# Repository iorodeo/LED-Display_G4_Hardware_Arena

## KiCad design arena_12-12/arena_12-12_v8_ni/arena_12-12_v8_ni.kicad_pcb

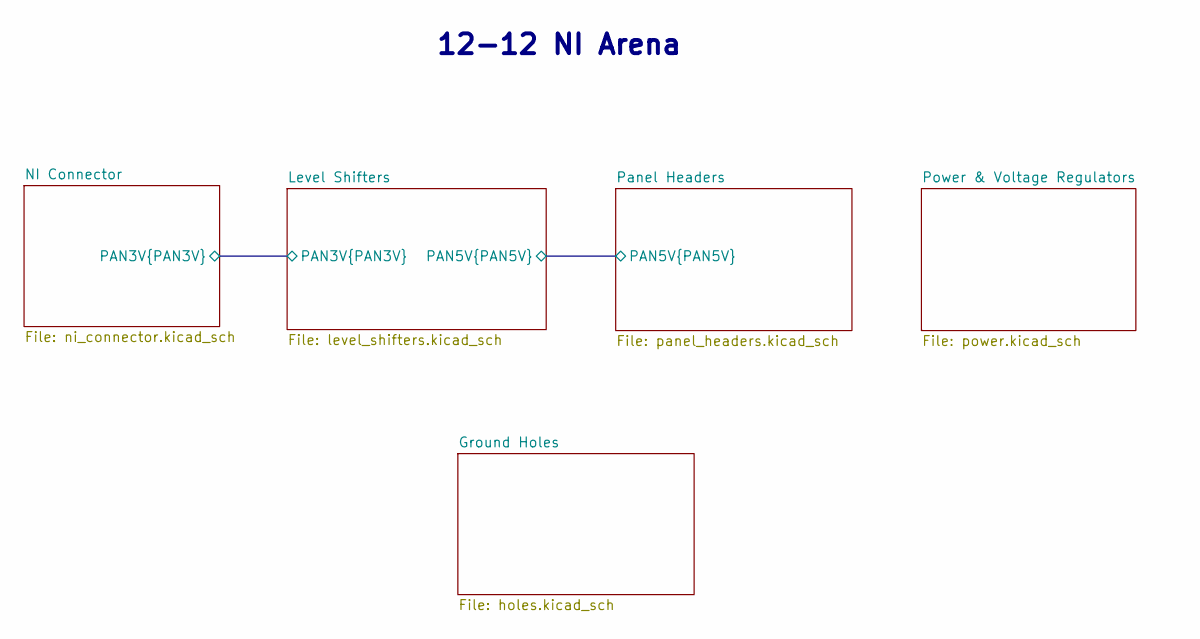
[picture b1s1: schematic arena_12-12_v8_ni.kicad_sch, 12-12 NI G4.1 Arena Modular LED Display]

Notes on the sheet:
12-12 NI Arena

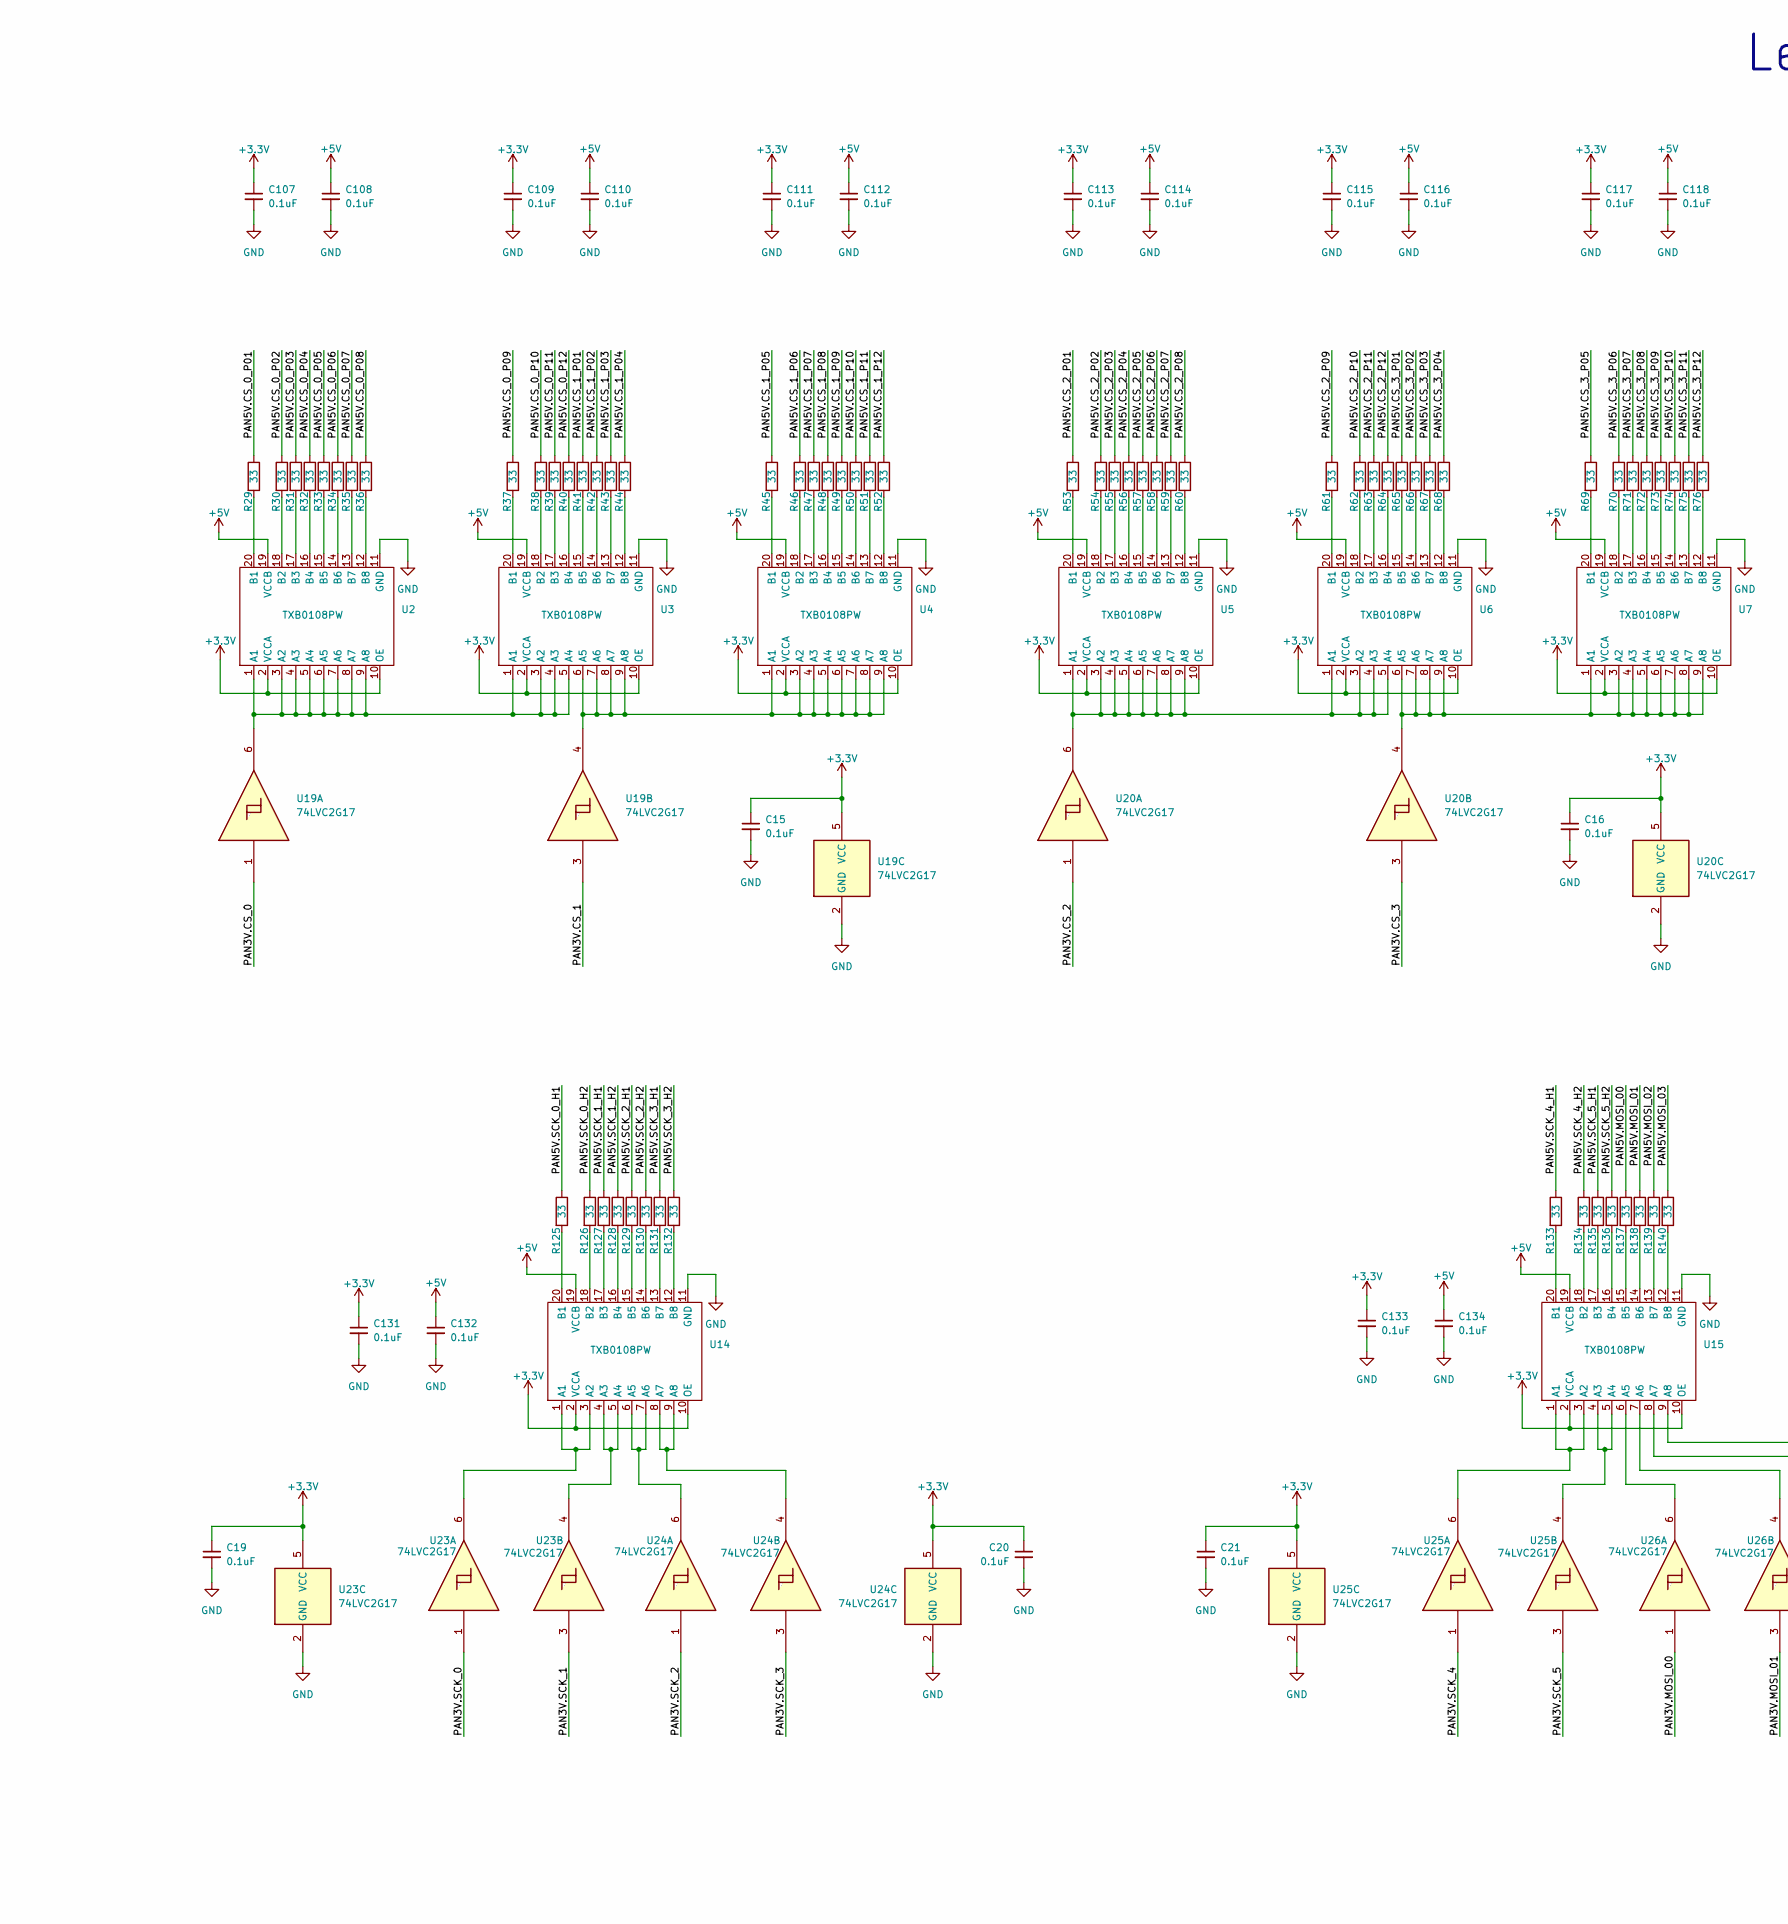
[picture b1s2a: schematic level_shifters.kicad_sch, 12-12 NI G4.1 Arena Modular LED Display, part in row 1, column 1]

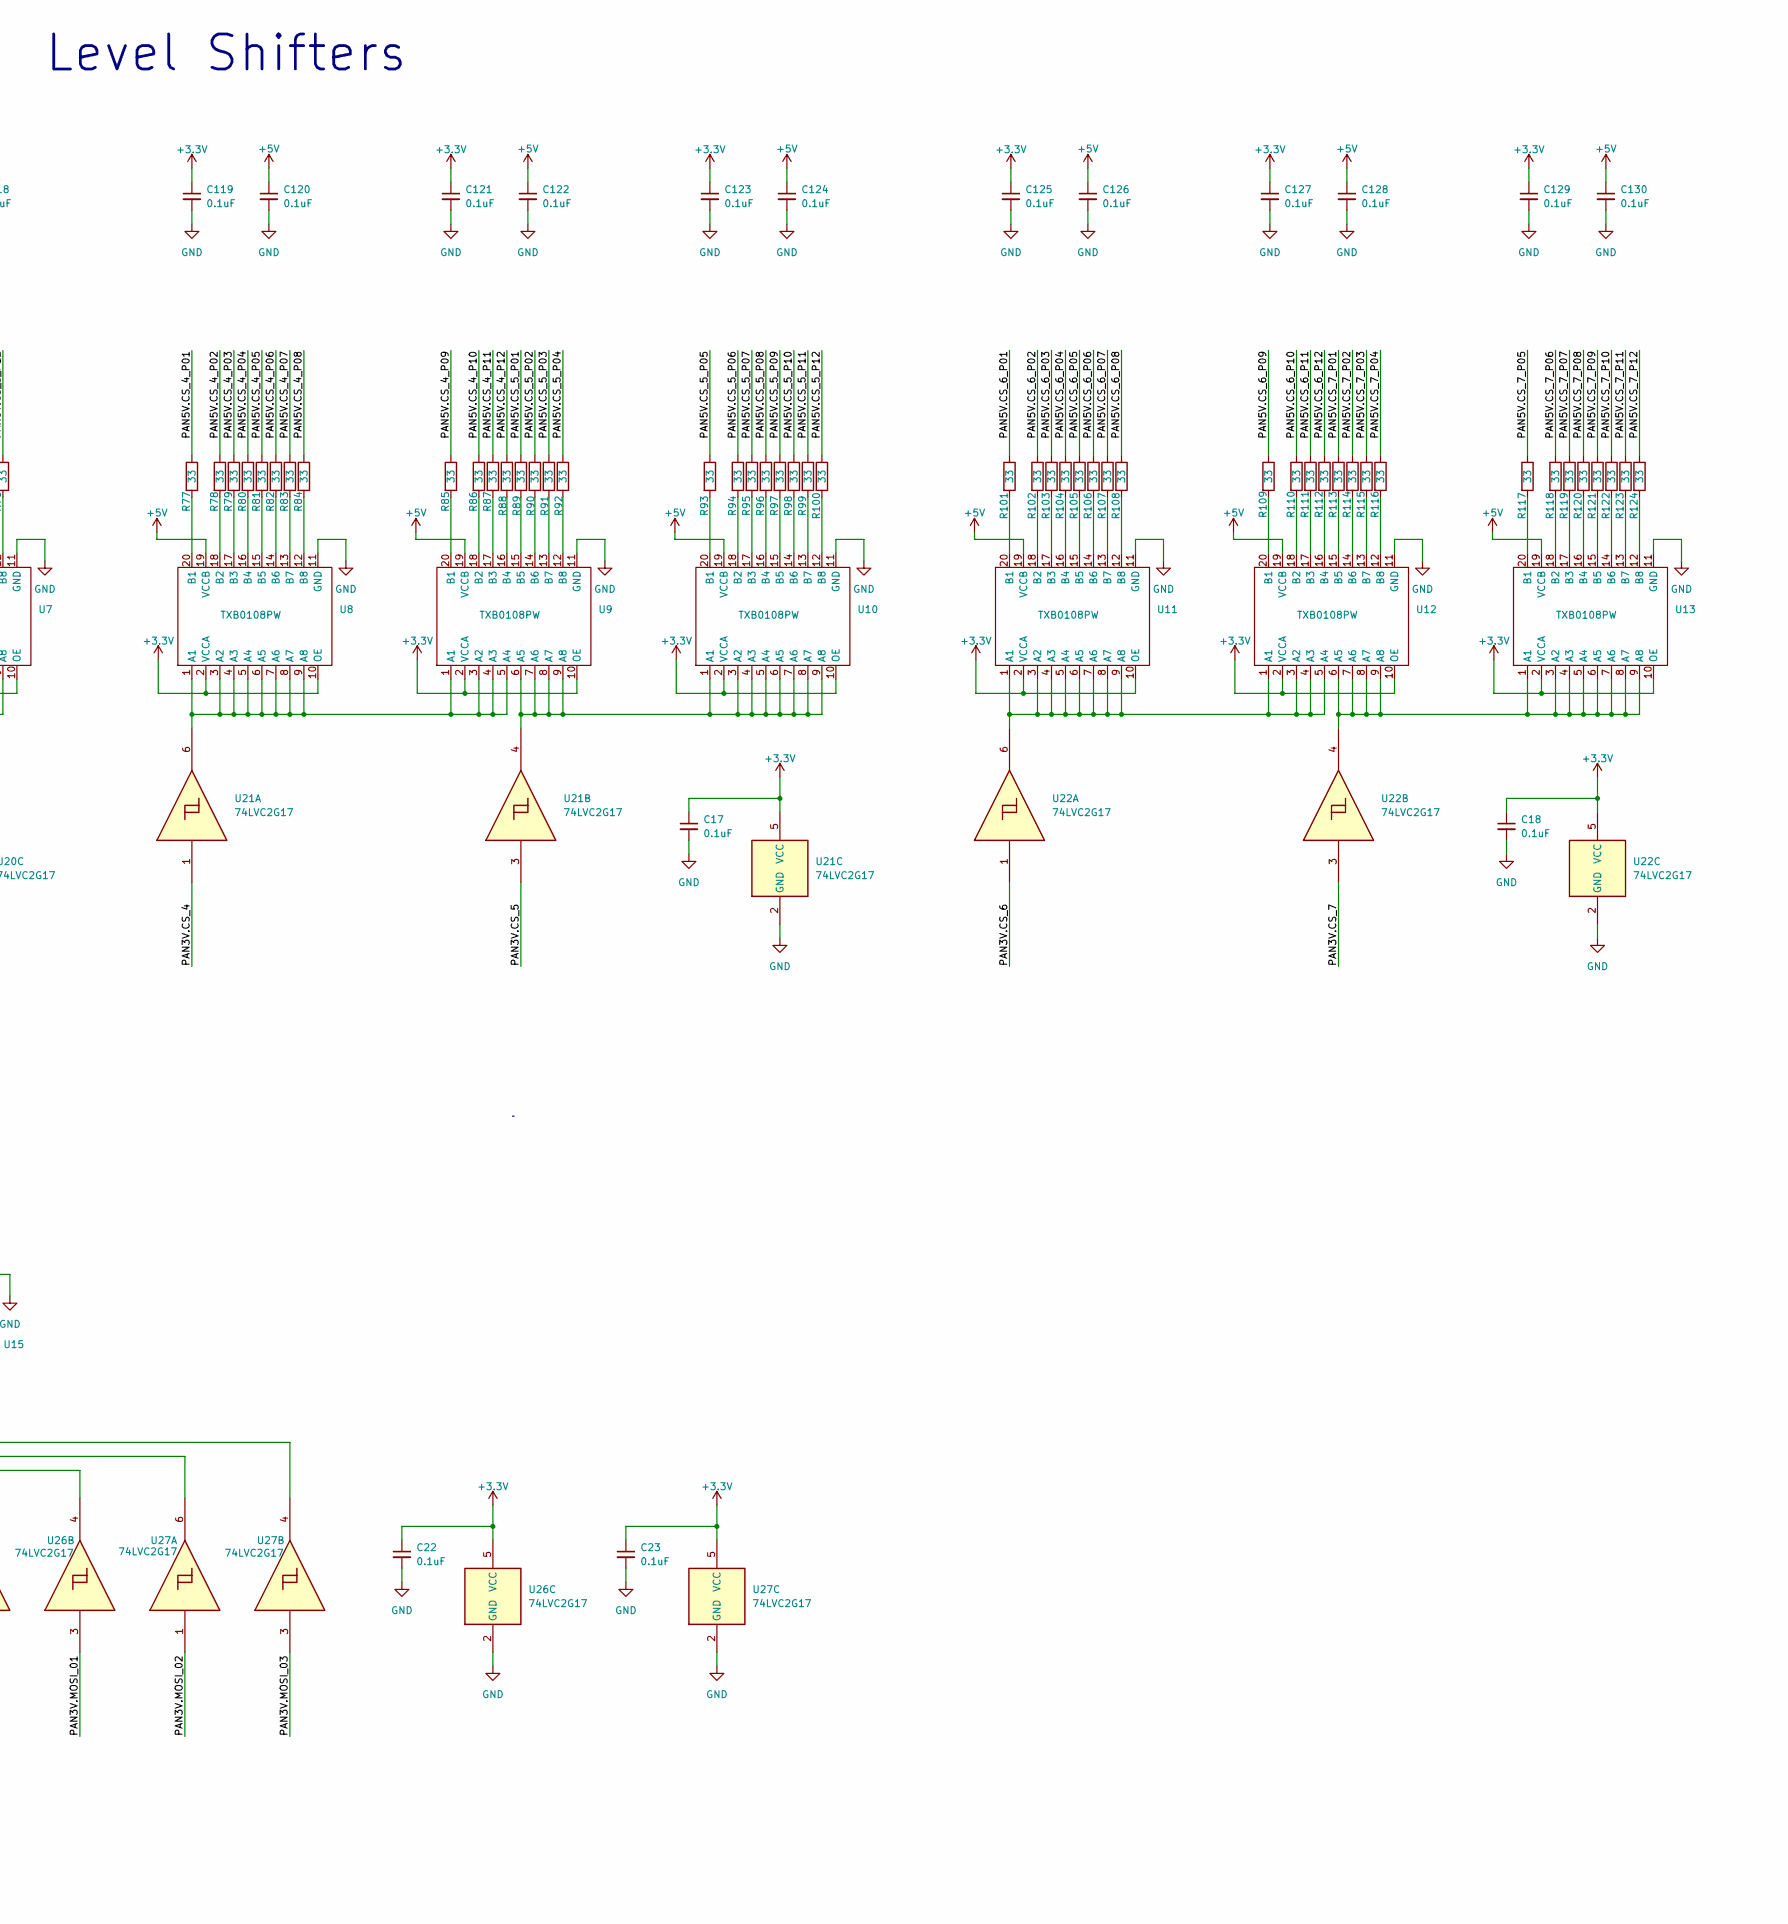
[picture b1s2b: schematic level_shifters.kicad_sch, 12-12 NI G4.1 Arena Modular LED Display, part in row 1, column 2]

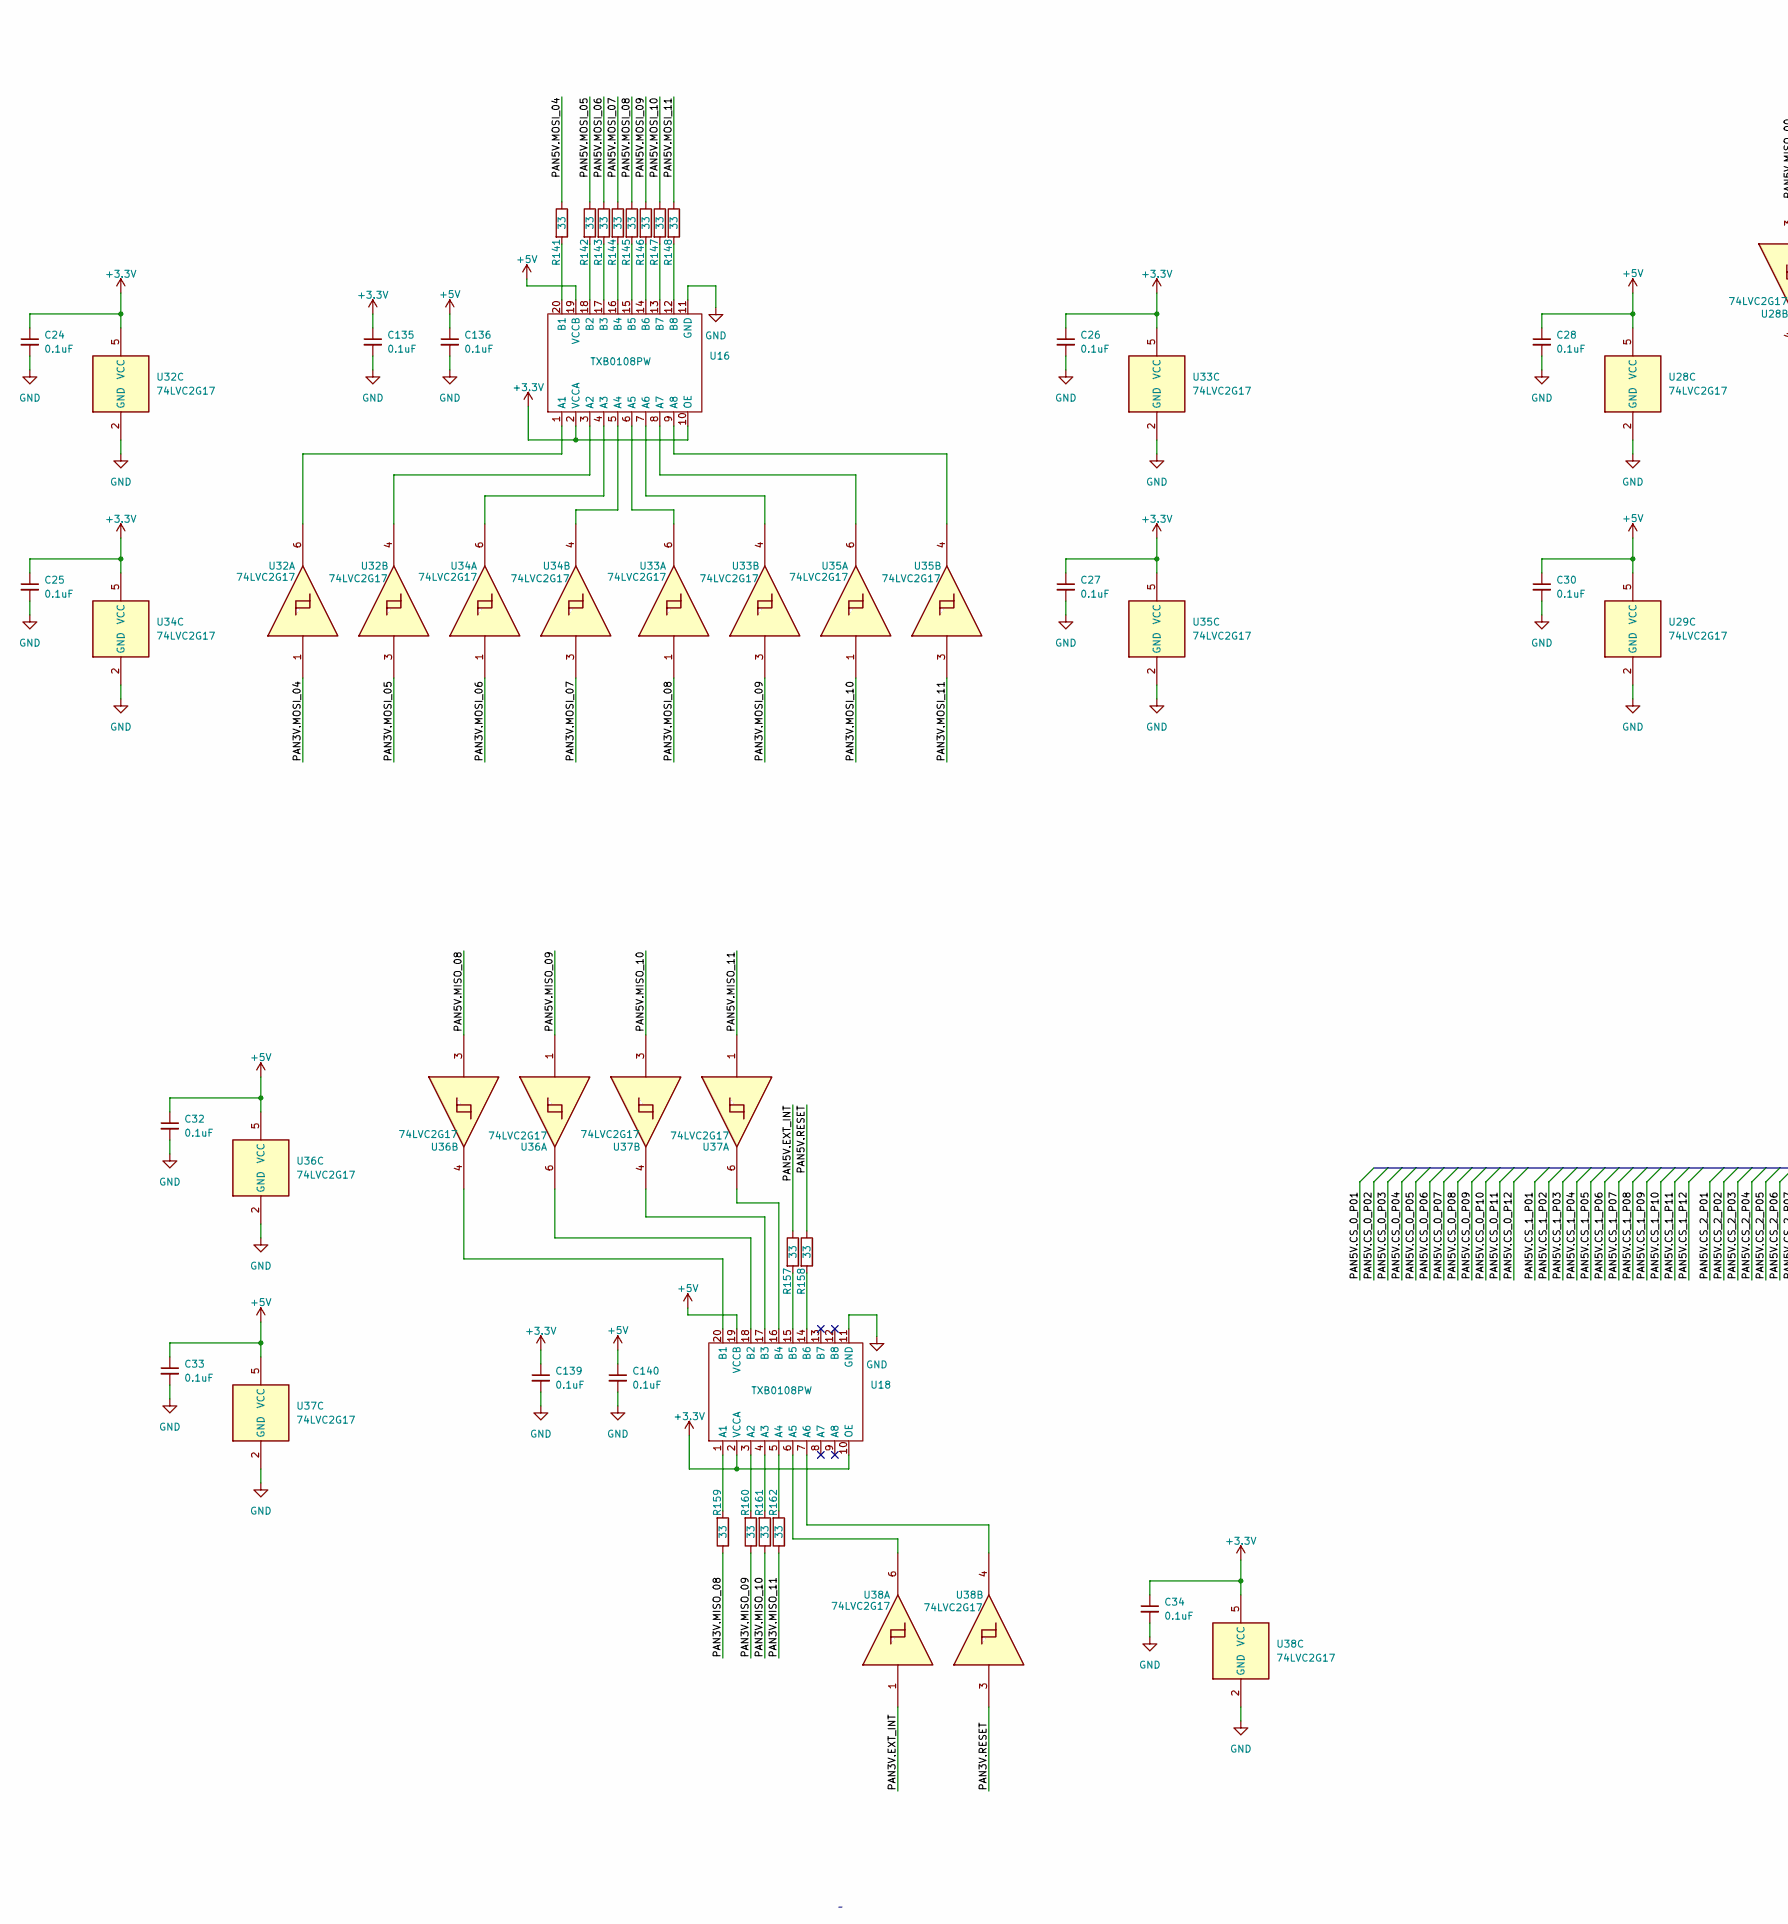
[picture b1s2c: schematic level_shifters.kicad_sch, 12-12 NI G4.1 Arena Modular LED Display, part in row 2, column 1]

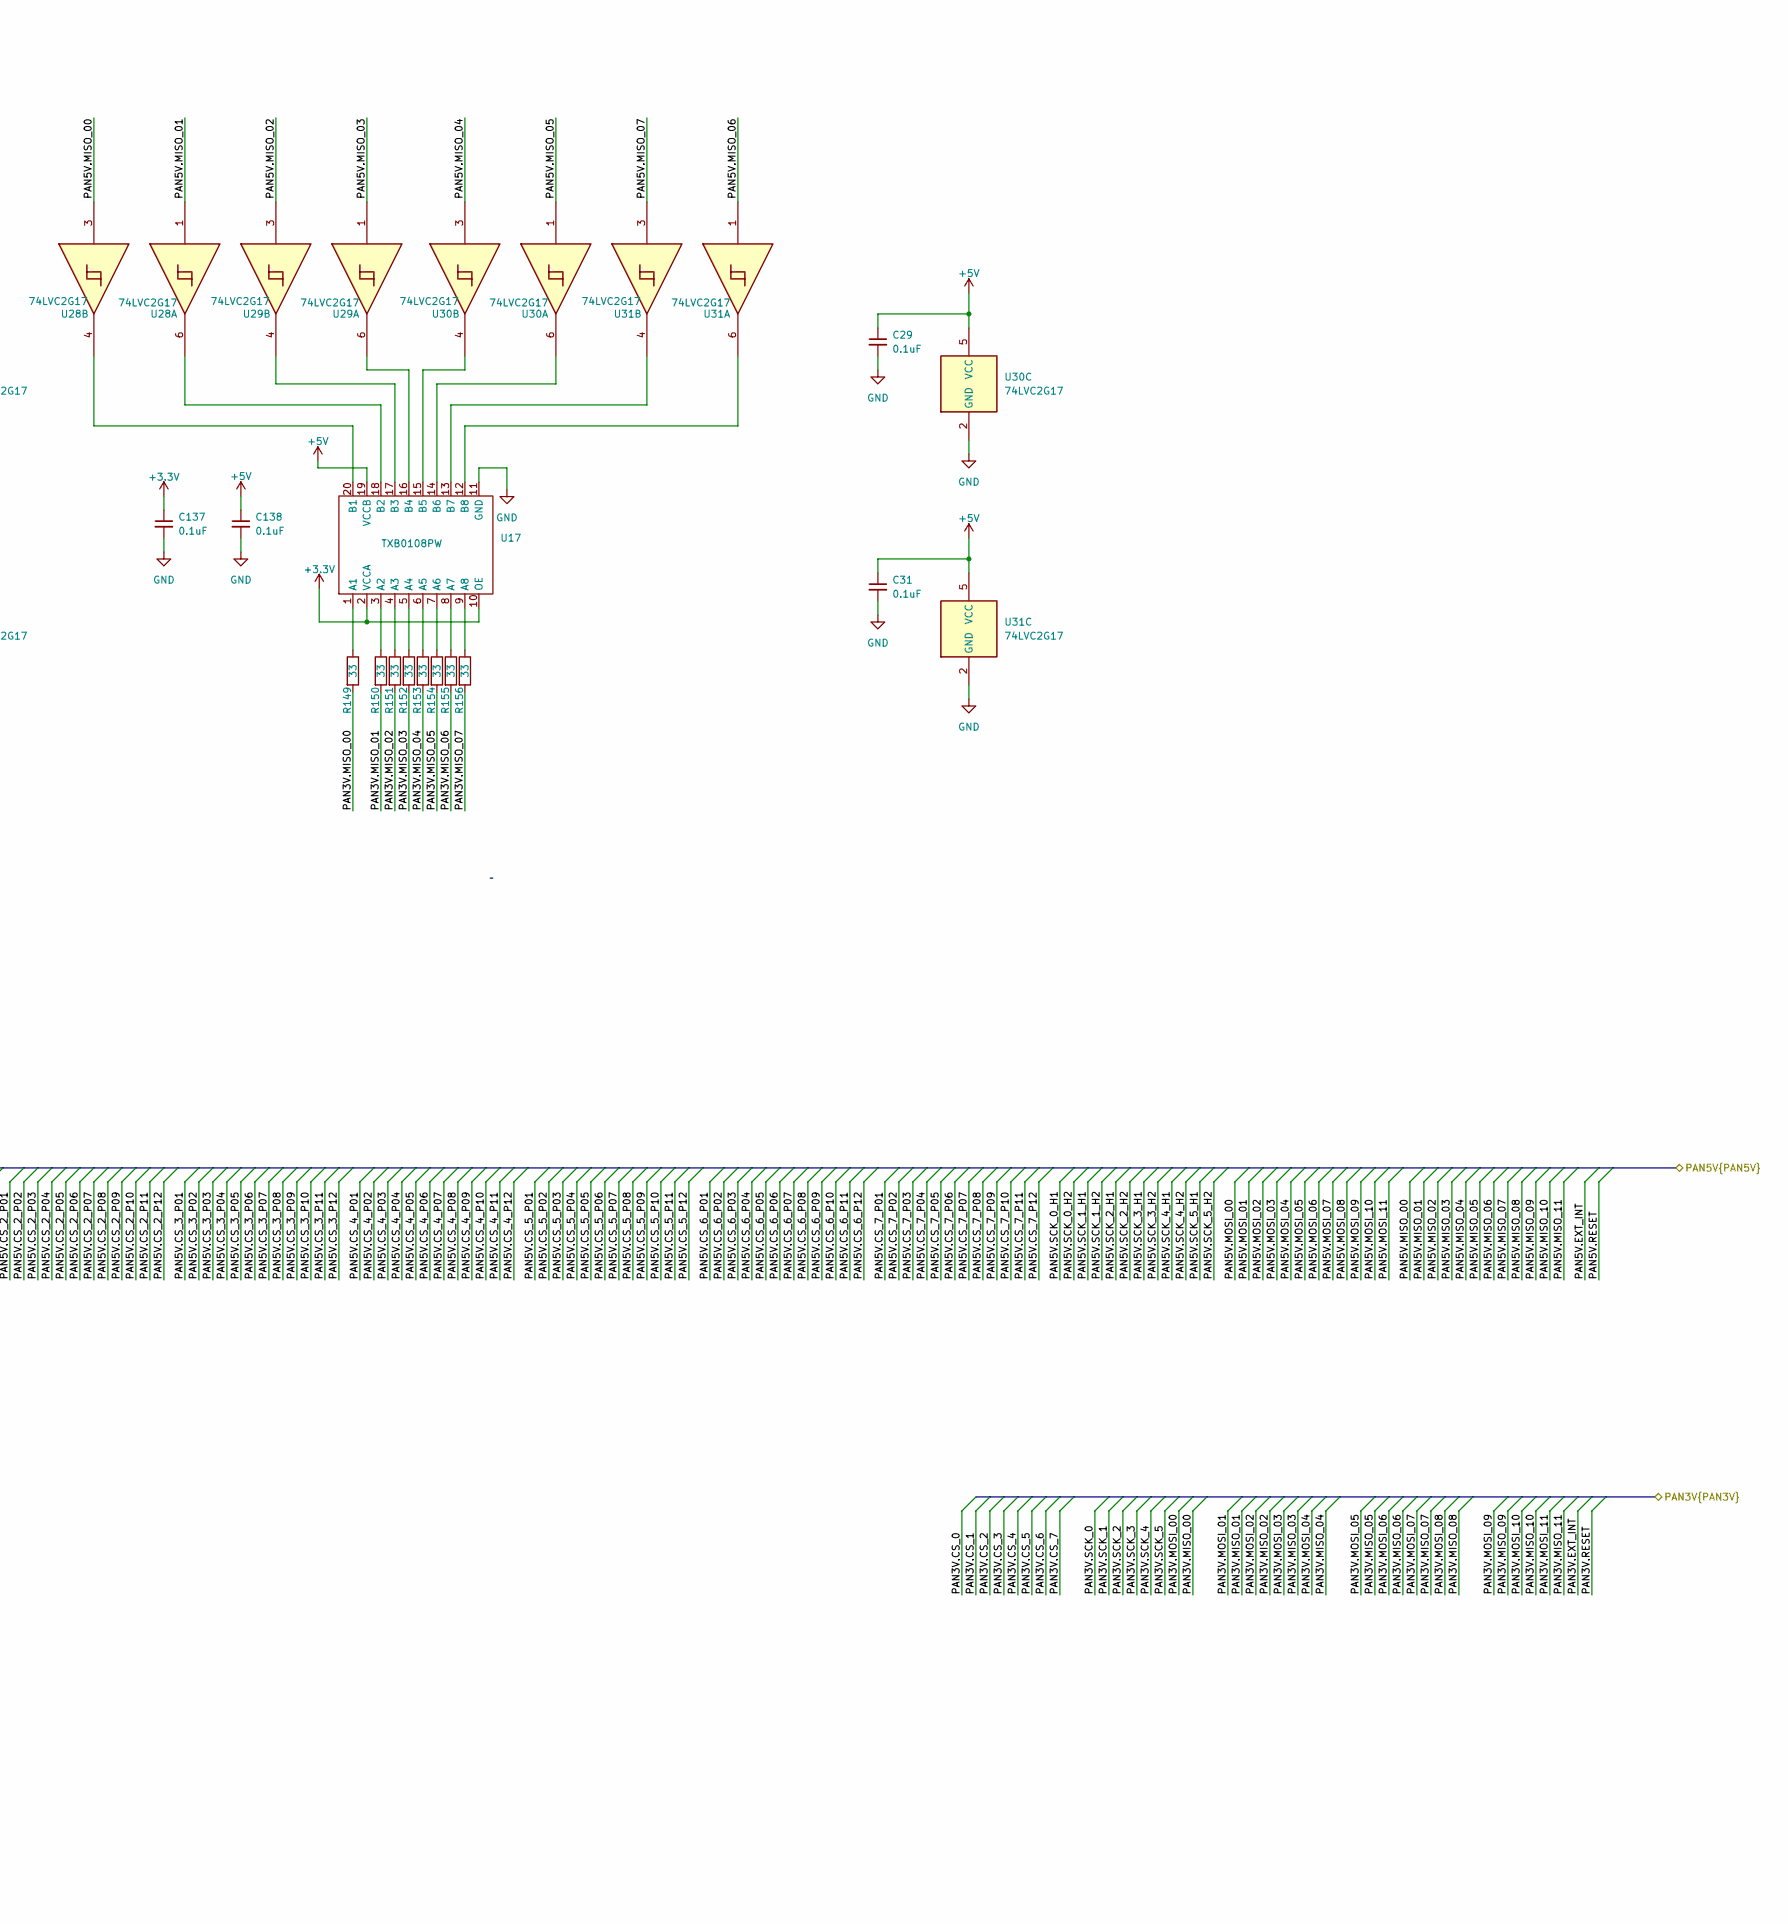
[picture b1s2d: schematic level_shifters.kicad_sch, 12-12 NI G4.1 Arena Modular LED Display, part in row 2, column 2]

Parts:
C15, C16, C17, C18, C19, C20, C21, C22, C23, C24, C25, C26, C27, C28, C29, C30, C31, C32, C33, C34, C107, C108, C109, C110, C111, C112, C113, C114, C115, C116, C117, C118, C119, C120, C121, C122, C123, C124, C125, C126, C127, C128, C129, C130, C131, C132, C133, C134, C135, C136, C137, C138, C139, C140: 0.1uF; C_0402_1005Metric; MPN CL05B104KO5NNNC; LCSC Part # C1525
R29, R30, R31, R32, R33, R34, R35, R36, R37, R38, R39, R40, R41, R42, R43, R44, R45, R46, R47, R48, R49, R50, R51, R52, R53, R54, R55, R56, R57, R58, R59, R60, R61, R62, R63, R64, R65, R66, R67, R68, R69, R70, R71, R72, R73, R74, R75, R76, R77, R78, R79, R80, R81, R82, R83, R84, R85, R86, R87, R88, R89, R90, R91, R92, R93, R94, R95, R96, R97, R98, R99, R100, R101, R102, R103, R104, R105, R106, R107, R108, R109, R110, R111, R112, R113, R114, R115, R116, R117, R118, R119, R120, R121, R122, R123, R124, R125, R126, R127, R128, R129, R130, R131, R132, R133, R134, R135, R136, R137, R138, R139, R140, R141, R142, R143, R144, R145, R146, R147, R148, R149, R150, R151, R152, R153, R154, R155, R156, R157, R158, R159, R160, R161, R162: 33; R_0402_1005Metric; MPN 0402WGF330JTCE; LCSC Part # C25105
U2, U3, U4, U5, U6, U7, U8, U9, U10, U11, U12, U13, U14, U15, U16, U17, U18: TXB0108PW; TSSOP-20_4.4x6.5mm_P0.65mm; MPN TXB0108PWR; Digikey PN 296-21527-2-ND
U19, U20, U21, U22, U23, U24, U25, U26, U27, U28, U29, U30, U31, U32, U33, U34, U35, U36, U37, U38: 74LVC2G17; SOT-23-6; MPN SN74LVC2G17DBVR; Digikey PN 296-SN74LVC2G17DBVRTR-ND

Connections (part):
+3.3V: C15.1, C16.1, C17.1, C18.1, C19.1, C20.1, C21.1, C22.1, C23.1, C24.1, C25.1, C26.1, C27.1, C34.1, C107.1, C109.1, C111.1, C113.1, C115.1, C117.1, C119.1, C121.1, C123.1, C125.1, C127.1, C129.1, C131.1, C133.1, C135.1, C137.1, C139.1, U2.2 (VCCA), U2.10 (OE), U3.2 (VCCA), U3.10 (OE), U4.2 (VCCA), U4.10 (OE), U5.2 (VCCA), U5.10 (OE), U6.2 (VCCA), U6.10 (OE), U7.2 (VCCA), U7.10 (OE), U8.2 (VCCA), U8.10 (OE), U9.2 (VCCA), U9.10 (OE), U10.2 (VCCA), U10.10 (OE), U11.2 (VCCA), U11.10 (OE), U12.2 (VCCA), U12.10 (OE), U13.2 (VCCA), U13.10 (OE), U14.2 (VCCA), U14.10 (OE), U15.2 (VCCA), U15.10 (OE), U16.2 (VCCA), U16.10 (OE), U17.2 (VCCA), U17.10 (OE), U18.2 (VCCA), U18.10 (OE), U19.5 (VCC), U20.5 (VCC), U21.5 (VCC), U22.5 (VCC), U23.5 (VCC), U24.5 (VCC), U25.5 (VCC), U26.5 (VCC), U27.5 (VCC), U32.5 (VCC), U33.5 (VCC), U34.5 (VCC), U35.5 (VCC), U38.5 (VCC); also elsewhere on the board
+5V: C28.1, C29.1, C30.1, C31.1, C32.1, C33.1, C108.1, C110.1, C112.1, C114.1, C116.1, C118.1, C120.1, C122.1, C124.1, C126.1, C128.1, C130.1, C132.1, C134.1, C136.1, C138.1, C140.1, U2.19 (VCCB), U3.19 (VCCB), U4.19 (VCCB), U5.19 (VCCB), U6.19 (VCCB), U7.19 (VCCB), U8.19 (VCCB), U9.19 (VCCB), U10.19 (VCCB), U11.19 (VCCB), U12.19 (VCCB), U13.19 (VCCB), U14.19 (VCCB), U15.19 (VCCB), U16.19 (VCCB), U17.19 (VCCB), U18.19 (VCCB), U28.5 (VCC), U29.5 (VCC), U30.5 (VCC), U31.5 (VCC), U36.5 (VCC), U37.5 (VCC); also elsewhere on the board
/Level Shifters/PAN3V.CS_0: U19.1; also elsewhere on the board
/Level Shifters/PAN3V.CS_1: U19.3; also elsewhere on the board
/Level Shifters/PAN3V.CS_2: U20.1; also elsewhere on the board
/Level Shifters/PAN3V.CS_3: U20.3; also elsewhere on the board
/Level Shifters/PAN3V.CS_4: U21.1; also elsewhere on the board
/Level Shifters/PAN3V.CS_5: U21.3; also elsewhere on the board
/Level Shifters/PAN3V.CS_6: U22.1; also elsewhere on the board
/Level Shifters/PAN3V.CS_7: U22.3; also elsewhere on the board
/Level Shifters/PAN3V.EXT_INT: U38.1; also elsewhere on the board
/Level Shifters/PAN3V.MISO_00: R149.2; also elsewhere on the board
/Level Shifters/PAN3V.MISO_01: R150.2; also elsewhere on the board
/Level Shifters/PAN3V.MISO_02: R151.2; also elsewhere on the board
/Level Shifters/PAN3V.MISO_03: R152.2; also elsewhere on the board
/Level Shifters/PAN3V.MISO_04: R153.2; also elsewhere on the board
/Level Shifters/PAN3V.MISO_05: R154.2; also elsewhere on the board
/Level Shifters/PAN3V.MISO_06: R155.2; also elsewhere on the board
/Level Shifters/PAN3V.MISO_07: R156.2; also elsewhere on the board
/Level Shifters/PAN3V.MISO_08: R159.1; also elsewhere on the board
/Level Shifters/PAN3V.MISO_09: R160.1; also elsewhere on the board
/Level Shifters/PAN3V.MISO_10: R161.1; also elsewhere on the board
/Level Shifters/PAN3V.MISO_11: R162.1; also elsewhere on the board
/Level Shifters/PAN3V.MOSI_00: U26.1; also elsewhere on the board
/Level Shifters/PAN3V.MOSI_01: U26.3; also elsewhere on the board
/Level Shifters/PAN3V.MOSI_02: U27.1; also elsewhere on the board
/Level Shifters/PAN3V.MOSI_03: U27.3; also elsewhere on the board
/Level Shifters/PAN3V.MOSI_04: U32.1; also elsewhere on the board
/Level Shifters/PAN3V.MOSI_05: U32.3; also elsewhere on the board
/Level Shifters/PAN3V.MOSI_06: U34.1; also elsewhere on the board
/Level Shifters/PAN3V.MOSI_07: U34.3; also elsewhere on the board
/Level Shifters/PAN3V.MOSI_08: U33.1; also elsewhere on the board
/Level Shifters/PAN3V.MOSI_09: U33.3; also elsewhere on the board
/Level Shifters/PAN3V.MOSI_10: U35.1; also elsewhere on the board
/Level Shifters/PAN3V.MOSI_11: U35.3; also elsewhere on the board
/Level Shifters/PAN3V.RESET: U38.3; also elsewhere on the board
/Level Shifters/PAN3V.SCK_0: U23.1; also elsewhere on the board
/Level Shifters/PAN3V.SCK_1: U23.3; also elsewhere on the board
/Level Shifters/PAN3V.SCK_2: U24.1; also elsewhere on the board
/Level Shifters/PAN3V.SCK_3: U24.3; also elsewhere on the board
/Level Shifters/PAN3V.SCK_4: U25.1; also elsewhere on the board
/Level Shifters/PAN3V.SCK_5: U25.3; also elsewhere on the board
/Level Shifters/PAN5V.CS_0_P01: R29.1; also elsewhere on the board
/Level Shifters/PAN5V.CS_0_P02: R30.1; also elsewhere on the board
/Level Shifters/PAN5V.CS_0_P03: R31.1; also elsewhere on the board
/Level Shifters/PAN5V.CS_0_P04: R32.1; also elsewhere on the board
/Level Shifters/PAN5V.CS_0_P05: R33.1; also elsewhere on the board
/Level Shifters/PAN5V.CS_0_P06: R34.1; also elsewhere on the board
/Level Shifters/PAN5V.CS_0_P07: R35.1; also elsewhere on the board
/Level Shifters/PAN5V.CS_0_P08: R36.1; also elsewhere on the board
/Level Shifters/PAN5V.CS_0_P09: R37.1; also elsewhere on the board
/Level Shifters/PAN5V.CS_0_P10: R38.1; also elsewhere on the board
/Level Shifters/PAN5V.CS_0_P11: R39.1; also elsewhere on the board
/Level Shifters/PAN5V.CS_0_P12: R40.1; also elsewhere on the board
/Level Shifters/PAN5V.CS_1_P01: R41.1; also elsewhere on the board
/Level Shifters/PAN5V.CS_1_P02: R42.1; also elsewhere on the board
/Level Shifters/PAN5V.CS_1_P03: R43.1; also elsewhere on the board
/Level Shifters/PAN5V.CS_1_P04: R44.1; also elsewhere on the board
/Level Shifters/PAN5V.CS_1_P05: R45.1; also elsewhere on the board
/Level Shifters/PAN5V.CS_1_P06: R46.1; also elsewhere on the board
/Level Shifters/PAN5V.CS_1_P07: R47.1; also elsewhere on the board
/Level Shifters/PAN5V.CS_1_P08: R48.1; also elsewhere on the board
/Level Shifters/PAN5V.CS_1_P09: R49.1; also elsewhere on the board
/Level Shifters/PAN5V.CS_1_P10: R50.1; also elsewhere on the board
/Level Shifters/PAN5V.CS_1_P11: R51.1; also elsewhere on the board
/Level Shifters/PAN5V.CS_1_P12: R52.1; also elsewhere on the board
/Level Shifters/PAN5V.CS_2_P01: R53.1; also elsewhere on the board
/Level Shifters/PAN5V.CS_2_P02: R54.1; also elsewhere on the board
/Level Shifters/PAN5V.CS_2_P03: R55.1; also elsewhere on the board
/Level Shifters/PAN5V.CS_2_P04: R56.1; also elsewhere on the board
/Level Shifters/PAN5V.CS_2_P05: R57.1; also elsewhere on the board
/Level Shifters/PAN5V.CS_2_P06: R58.1; also elsewhere on the board
/Level Shifters/PAN5V.CS_2_P07: R59.1; also elsewhere on the board
/Level Shifters/PAN5V.CS_2_P08: R60.1; also elsewhere on the board
/Level Shifters/PAN5V.CS_2_P09: R61.1; also elsewhere on the board
/Level Shifters/PAN5V.CS_2_P10: R62.1; also elsewhere on the board
/Level Shifters/PAN5V.CS_2_P11: R63.1; also elsewhere on the board
/Level Shifters/PAN5V.CS_2_P12: R64.1; also elsewhere on the board
/Level Shifters/PAN5V.CS_3_P01: R65.1; also elsewhere on the board
/Level Shifters/PAN5V.CS_3_P02: R66.1; also elsewhere on the board
/Level Shifters/PAN5V.CS_3_P03: R67.1; also elsewhere on the board
/Level Shifters/PAN5V.CS_3_P04: R68.1; also elsewhere on the board
/Level Shifters/PAN5V.CS_3_P05: R69.1; also elsewhere on the board
/Level Shifters/PAN5V.CS_3_P06: R70.1; also elsewhere on the board
/Level Shifters/PAN5V.CS_3_P07: R71.1; also elsewhere on the board
/Level Shifters/PAN5V.CS_3_P08: R72.1; also elsewhere on the board
/Level Shifters/PAN5V.CS_3_P09: R73.1; also elsewhere on the board
/Level Shifters/PAN5V.CS_3_P10: R74.1; also elsewhere on the board
/Level Shifters/PAN5V.CS_3_P11: R75.1; also elsewhere on the board
/Level Shifters/PAN5V.CS_3_P12: R76.1; also elsewhere on the board
/Level Shifters/PAN5V.CS_4_P01: R77.1; also elsewhere on the board
/Level Shifters/PAN5V.CS_4_P02: R78.1; also elsewhere on the board
/Level Shifters/PAN5V.CS_4_P03: R79.1; also elsewhere on the board
/Level Shifters/PAN5V.CS_4_P04: R80.1; also elsewhere on the board
/Level Shifters/PAN5V.CS_4_P05: R81.1; also elsewhere on the board
/Level Shifters/PAN5V.CS_4_P06: R82.1; also elsewhere on the board
/Level Shifters/PAN5V.CS_4_P07: R83.1; also elsewhere on the board
/Level Shifters/PAN5V.CS_4_P08: R84.1; also elsewhere on the board
/Level Shifters/PAN5V.CS_4_P09: R85.1; also elsewhere on the board
/Level Shifters/PAN5V.CS_4_P10: R86.1; also elsewhere on the board
/Level Shifters/PAN5V.CS_4_P11: R87.1; also elsewhere on the board
/Level Shifters/PAN5V.CS_4_P12: R88.1; also elsewhere on the board
/Level Shifters/PAN5V.CS_5_P01: R89.1; also elsewhere on the board
/Level Shifters/PAN5V.CS_5_P02: R90.1; also elsewhere on the board
/Level Shifters/PAN5V.CS_5_P03: R91.1; also elsewhere on the board
/Level Shifters/PAN5V.CS_5_P04: R92.1; also elsewhere on the board
/Level Shifters/PAN5V.CS_5_P05: R93.1; also elsewhere on the board
/Level Shifters/PAN5V.CS_5_P06: R94.1; also elsewhere on the board
/Level Shifters/PAN5V.CS_5_P07: R95.1; also elsewhere on the board
/Level Shifters/PAN5V.CS_5_P08: R96.1; also elsewhere on the board
/Level Shifters/PAN5V.CS_5_P09: R97.1; also elsewhere on the board
/Level Shifters/PAN5V.CS_5_P10: R98.1; also elsewhere on the board
/Level Shifters/PAN5V.CS_5_P11: R99.1; also elsewhere on the board
/Level Shifters/PAN5V.CS_5_P12: R100.1; also elsewhere on the board
/Level Shifters/PAN5V.CS_6_P01: R101.1; also elsewhere on the board
/Level Shifters/PAN5V.CS_6_P02: R102.1; also elsewhere on the board
/Level Shifters/PAN5V.CS_6_P03: R103.1; also elsewhere on the board
/Level Shifters/PAN5V.CS_6_P04: R104.1; also elsewhere on the board
/Level Shifters/PAN5V.CS_6_P05: R105.1; also elsewhere on the board
/Level Shifters/PAN5V.CS_6_P06: R106.1; also elsewhere on the board
/Level Shifters/PAN5V.CS_6_P07: R107.1; also elsewhere on the board
/Level Shifters/PAN5V.CS_6_P08: R108.1; also elsewhere on the board
/Level Shifters/PAN5V.CS_6_P09: R109.1; also elsewhere on the board
/Level Shifters/PAN5V.CS_6_P10: R110.1; also elsewhere on the board
/Level Shifters/PAN5V.CS_6_P11: R111.1; also elsewhere on the board
/Level Shifters/PAN5V.CS_6_P12: R112.1; also elsewhere on the board
/Level Shifters/PAN5V.CS_7_P01: R113.1; also elsewhere on the board
/Level Shifters/PAN5V.CS_7_P02: R114.1; also elsewhere on the board
/Level Shifters/PAN5V.CS_7_P03: R115.1; also elsewhere on the board
/Level Shifters/PAN5V.CS_7_P04: R116.1; also elsewhere on the board
/Level Shifters/PAN5V.CS_7_P05: R117.1; also elsewhere on the board
/Level Shifters/PAN5V.CS_7_P06: R118.1; also elsewhere on the board
/Level Shifters/PAN5V.CS_7_P07: R119.1; also elsewhere on the board
/Level Shifters/PAN5V.CS_7_P08: R120.1; also elsewhere on the board
/Level Shifters/PAN5V.CS_7_P09: R121.1; also elsewhere on the board
/Level Shifters/PAN5V.CS_7_P10: R122.1; also elsewhere on the board
/Level Shifters/PAN5V.CS_7_P11: R123.1; also elsewhere on the board
/Level Shifters/PAN5V.CS_7_P12: R124.1; also elsewhere on the board
/Level Shifters/PAN5V.EXT_INT: R157.1; also elsewhere on the board
/Level Shifters/PAN5V.MISO_00: U28.3; also elsewhere on the board
/Level Shifters/PAN5V.MISO_01: U28.1; also elsewhere on the board
/Level Shifters/PAN5V.MISO_02: U29.3; also elsewhere on the board
/Level Shifters/PAN5V.MISO_03: U29.1; also elsewhere on the board
/Level Shifters/PAN5V.MISO_04: U30.3; also elsewhere on the board
/Level Shifters/PAN5V.MISO_05: U30.1; also elsewhere on the board
/Level Shifters/PAN5V.MISO_06: U31.1; also elsewhere on the board
/Level Shifters/PAN5V.MISO_07: U31.3; also elsewhere on the board
/Level Shifters/PAN5V.MISO_08: U36.3; also elsewhere on the board
/Level Shifters/PAN5V.MISO_09: U36.1; also elsewhere on the board
/Level Shifters/PAN5V.MISO_10: U37.3; also elsewhere on the board
/Level Shifters/PAN5V.MISO_11: U37.1; also elsewhere on the board
/Level Shifters/PAN5V.MOSI_00: R137.1; also elsewhere on the board
/Level Shifters/PAN5V.MOSI_01: R138.1; also elsewhere on the board
/Level Shifters/PAN5V.MOSI_02: R139.1; also elsewhere on the board
/Level Shifters/PAN5V.MOSI_03: R140.1; also elsewhere on the board
/Level Shifters/PAN5V.MOSI_04: R141.1; also elsewhere on the board
/Level Shifters/PAN5V.MOSI_05: R142.1; also elsewhere on the board
/Level Shifters/PAN5V.MOSI_06: R143.1; also elsewhere on the board
/Level Shifters/PAN5V.MOSI_07: R144.1; also elsewhere on the board
/Level Shifters/PAN5V.MOSI_08: R145.1; also elsewhere on the board
/Level Shifters/PAN5V.MOSI_09: R146.1; also elsewhere on the board
/Level Shifters/PAN5V.MOSI_10: R147.1; also elsewhere on the board
/Level Shifters/PAN5V.MOSI_11: R148.1; also elsewhere on the board
/Level Shifters/PAN5V.RESET: R158.1; also elsewhere on the board
/Level Shifters/PAN5V.SCK_0_H1: R125.1; also elsewhere on the board
/Level Shifters/PAN5V.SCK_0_H2: R126.1; also elsewhere on the board
/Level Shifters/PAN5V.SCK_1_H1: R127.1; also elsewhere on the board
/Level Shifters/PAN5V.SCK_1_H2: R128.1; also elsewhere on the board
/Level Shifters/PAN5V.SCK_2_H1: R129.1; also elsewhere on the board
/Level Shifters/PAN5V.SCK_2_H2: R130.1; also elsewhere on the board
/Level Shifters/PAN5V.SCK_3_H1: R131.1; also elsewhere on the board
/Level Shifters/PAN5V.SCK_3_H2: R132.1; also elsewhere on the board
/Level Shifters/PAN5V.SCK_4_H1: R133.1; also elsewhere on the board
/Level Shifters/PAN5V.SCK_4_H2: R134.1; also elsewhere on the board
/Level Shifters/PAN5V.SCK_5_H1: R135.1; also elsewhere on the board
/Level Shifters/PAN5V.SCK_5_H2: R136.1; also elsewhere on the board
GND: C15.2, C16.2, C17.2, C18.2, C19.2, C20.2, C21.2, C22.2, C23.2, C24.2, C25.2, C26.2, C27.2, C28.2, C29.2, C30.2, C31.2, C32.2, C33.2, C34.2, C107.2, C108.2, C109.2, C110.2, C111.2, C112.2, C113.2, C114.2, C115.2, C116.2, C117.2, C118.2, C119.2, C120.2, C121.2, C122.2, C123.2, C124.2, C125.2, C126.2, C127.2, C128.2, C129.2, C130.2, C131.2, C132.2, C133.2, C134.2, C135.2, C136.2, C137.2, C138.2, C139.2, C140.2, U2.11 (GND), U3.11 (GND), U4.11 (GND), U5.11 (GND), U6.11 (GND), U7.11 (GND), U8.11 (GND), U9.11 (GND), U10.11 (GND), U11.11 (GND), U12.11 (GND), U13.11 (GND), U14.11 (GND), U15.11 (GND), U16.11 (GND), U17.11 (GND), U18.11 (GND), U19.2 (GND), U20.2 (GND), U21.2 (GND), U22.2 (GND), U23.2 (GND), U24.2 (GND), U25.2 (GND), U26.2 (GND), U27.2 (GND), U28.2 (GND)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; also elsewhere on the board
unnamed: U2.1 (A1), U2.3 (A2), U2.4 (A3), U2.5 (A4), U2.6 (A5), U2.7 (A6), U2.8 (A7), U2.9 (A8), U3.1 (A1), U3.3 (A2), U3.4 (A3), U3.5 (A4), U19.6
unnamed: R29.2, U2.20 (B1)
unnamed: R30.2, U2.18 (B2)
unnamed: R31.2, U2.17 (B3)
unnamed: R32.2, U2.16 (B4)
unnamed: R33.2, U2.15 (B5)
unnamed: R34.2, U2.14 (B6)
unnamed: R35.2, U2.13 (B7)
unnamed: R36.2, U2.12 (B8)
unnamed: U3.6 (A5), U3.7 (A6), U3.8 (A7), U3.9 (A8), U4.1 (A1), U4.3 (A2), U4.4 (A3), U4.5 (A4), U4.6 (A5), U4.7 (A6), U4.8 (A7), U4.9 (A8), U19.4
unnamed: R37.2, U3.20 (B1)
unnamed: R38.2, U3.18 (B2)
unnamed: R39.2, U3.17 (B3)
unnamed: R40.2, U3.16 (B4)
unnamed: R41.2, U3.15 (B5)
unnamed: R42.2, U3.14 (B6)
unnamed: R43.2, U3.13 (B7)
unnamed: R44.2, U3.12 (B8)
unnamed: R45.2, U4.20 (B1)
unnamed: R46.2, U4.18 (B2)
unnamed: R47.2, U4.17 (B3)
unnamed: R48.2, U4.16 (B4)
unnamed: R49.2, U4.15 (B5)
unnamed: R50.2, U4.14 (B6)
unnamed: R51.2, U4.13 (B7)
unnamed: R52.2, U4.12 (B8)
unnamed: U5.1 (A1), U5.3 (A2), U5.4 (A3), U5.5 (A4), U5.6 (A5), U5.7 (A6), U5.8 (A7), U5.9 (A8), U6.1 (A1), U6.3 (A2), U6.4 (A3), U6.5 (A4), U20.6
unnamed: R53.2, U5.20 (B1)
unnamed: R54.2, U5.18 (B2)
unnamed: R55.2, U5.17 (B3)
unnamed: R56.2, U5.16 (B4)
unnamed: R57.2, U5.15 (B5)
unnamed: R58.2, U5.14 (B6)
unnamed: R59.2, U5.13 (B7)
unnamed: R60.2, U5.12 (B8)
unnamed: U6.6 (A5), U6.7 (A6), U6.8 (A7), U6.9 (A8), U7.1 (A1), U7.3 (A2), U7.4 (A3), U7.5 (A4), U7.6 (A5), U7.7 (A6), U7.8 (A7), U7.9 (A8), U20.4
unnamed: R61.2, U6.20 (B1)
unnamed: R62.2, U6.18 (B2)
unnamed: R63.2, U6.17 (B3)
unnamed: R64.2, U6.16 (B4)
unnamed: R65.2, U6.15 (B5)
unnamed: R66.2, U6.14 (B6)
unnamed: R67.2, U6.13 (B7)
unnamed: R68.2, U6.12 (B8)
unnamed: R69.2, U7.20 (B1)
unnamed: R70.2, U7.18 (B2)
unnamed: R71.2, U7.17 (B3)
unnamed: R72.2, U7.16 (B4)
unnamed: R73.2, U7.15 (B5)
unnamed: R74.2, U7.14 (B6)
unnamed: R75.2, U7.13 (B7)
unnamed: R76.2, U7.12 (B8)
unnamed: U8.1 (A1), U8.3 (A2), U8.4 (A3), U8.5 (A4), U8.6 (A5), U8.7 (A6), U8.8 (A7), U8.9 (A8), U9.1 (A1), U9.3 (A2), U9.4 (A3), U9.5 (A4), U21.6
unnamed: R77.2, U8.20 (B1)
unnamed: R78.2, U8.18 (B2)
unnamed: R79.2, U8.17 (B3)
unnamed: R80.2, U8.16 (B4)
unnamed: R81.2, U8.15 (B5)
unnamed: R82.2, U8.14 (B6)
unnamed: R83.2, U8.13 (B7)
unnamed: R84.2, U8.12 (B8)
unnamed: R85.2, U9.20 (B1)
unnamed: R86.2, U9.18 (B2)
unnamed: R87.2, U9.17 (B3)
unnamed: R88.2, U9.16 (B4)
unnamed: R89.2, U9.15 (B5)
unnamed: R90.2, U9.14 (B6)
unnamed: R91.2, U9.13 (B7)
unnamed: R92.2, U9.12 (B8)
unnamed: U9.6 (A5), U9.7 (A6), U9.8 (A7), U9.9 (A8), U10.1 (A1), U10.3 (A2), U10.4 (A3), U10.5 (A4), U10.6 (A5), U10.7 (A6), U10.8 (A7), U10.9 (A8), U21.4
unnamed: R93.2, U10.20 (B1)
unnamed: R94.2, U10.18 (B2)
unnamed: R95.2, U10.17 (B3)
unnamed: R96.2, U10.16 (B4)
unnamed: R97.2, U10.15 (B5)
unnamed: R98.2, U10.14 (B6)
unnamed: R99.2, U10.13 (B7)
unnamed: R100.2, U10.12 (B8)
unnamed: U11.1 (A1), U11.3 (A2), U11.4 (A3), U11.5 (A4), U11.6 (A5), U11.7 (A6), U11.8 (A7), U11.9 (A8), U12.1 (A1), U12.3 (A2), U12.4 (A3), U12.5 (A4), U22.6
unnamed: R101.2, U11.20 (B1)
unnamed: R102.2, U11.18 (B2)
unnamed: R103.2, U11.17 (B3)
unnamed: R104.2, U11.16 (B4)
unnamed: R105.2, U11.15 (B5)
unnamed: R106.2, U11.14 (B6)
unnamed: R107.2, U11.13 (B7)
unnamed: R108.2, U11.12 (B8)
unnamed: U12.6 (A5), U12.7 (A6), U12.8 (A7), U12.9 (A8), U13.1 (A1), U13.3 (A2), U13.4 (A3), U13.5 (A4), U13.6 (A5), U13.7 (A6), U13.8 (A7), U13.9 (A8), U22.4
unnamed: R109.2, U12.20 (B1)
unnamed: R110.2, U12.18 (B2)
unnamed: R111.2, U12.17 (B3)
unnamed: R112.2, U12.16 (B4)
unnamed: R113.2, U12.15 (B5)
unnamed: R114.2, U12.14 (B6)
unnamed: R115.2, U12.13 (B7)
unnamed: R116.2, U12.12 (B8)
unnamed: R117.2, U13.20 (B1)
unnamed: R118.2, U13.18 (B2)
unnamed: R119.2, U13.17 (B3)
unnamed: R120.2, U13.16 (B4)
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
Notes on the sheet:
Level Shifters
